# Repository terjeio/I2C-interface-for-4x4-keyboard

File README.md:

# I2C interface for 4x4 (or 5x5) keyboard with partial support for 2-key rollover and autorepeat.
Based on a Texas Instruments MSP430G2553 processor, uses a GPIO pin for signalling keypress events to host.
Example PCB is a KiCad project for the 20-pin DIP version MSP430G2553.

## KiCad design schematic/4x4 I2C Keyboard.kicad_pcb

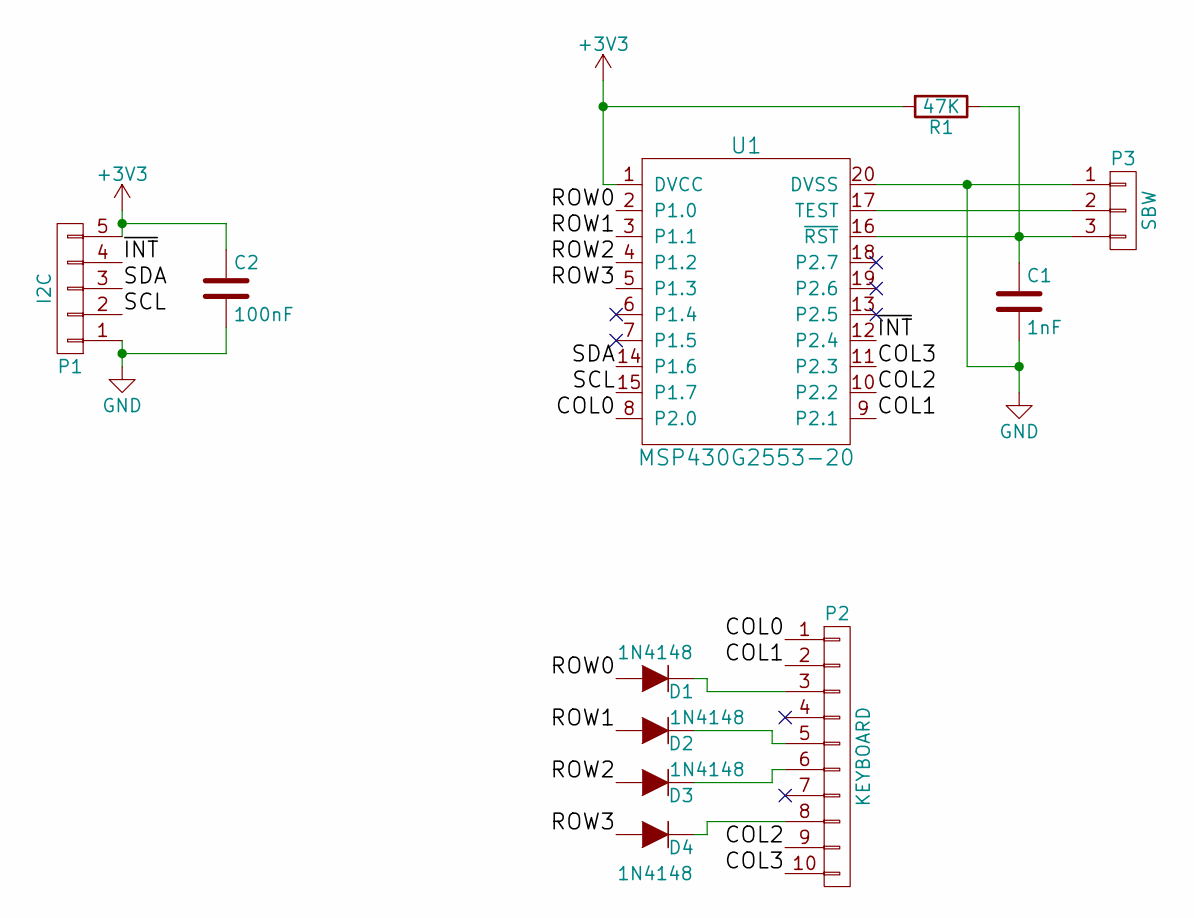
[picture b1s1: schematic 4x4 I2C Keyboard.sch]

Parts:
C1: 1nF; C_Disc_D5.0mm_W2.5mm_P2.50mm
C2: 100nF; C_Disc_D5.0mm_W2.5mm_P2.50mm
D1, D2, D3, D4: 1N4148; D_DO-41_SOD81_P7.62mm_Horizontal
P1: I2C; Pin_Header_Straight_1x05_Pitch2.54mm
P2: KEYBOARD; Pin_Header_Straight_1x10_Pitch2.54mm
P3: SBW; Pin_Header_Straight_1x03_Pitch2.54mm
R1: 47K; R_Axial_DIN0207_L6.3mm_D2.5mm_P10.16mm_Horizontal
U1: MSP430G2553-20; DIP-20_W7.62mm_Socket

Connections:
+3V3: C2.1, P1.5, R1.2, U1.1 (DVCC)
/COL0: P2.1, U1.8 (P2.0)
/COL1: P2.2, U1.9 (P2.1)
/COL2: P2.9, U1.10 (P2.2)
/COL3: P2.10, U1.11 (P2.3)
/ROW0: D1.2 (A), U1.2 (P1.0)
/ROW1: D2.2 (A), U1.3 (P1.1)
/ROW2: D3.2 (A), U1.4 (P1.2)
/ROW3: D4.2 (A), U1.5 (P1.3)
/SCL: P1.2, U1.15 (P1.7)
/SDA: P1.3, U1.14 (P1.6)
/~INT: P1.4, U1.12 (P2.4)
GND: C1.2, C2.2, P1.1, P3.1, U1.20 (DVSS)
unnamed: C1.1, P3.3, R1.1, U1.16 (~RST~)
unnamed: D1.1 (K), P2.3
unnamed: D2.1 (K), P2.5
unnamed: D3.1 (K), P2.6
unnamed: D4.1 (K), P2.8
unnamed: P3.2, U1.17 (TEST)

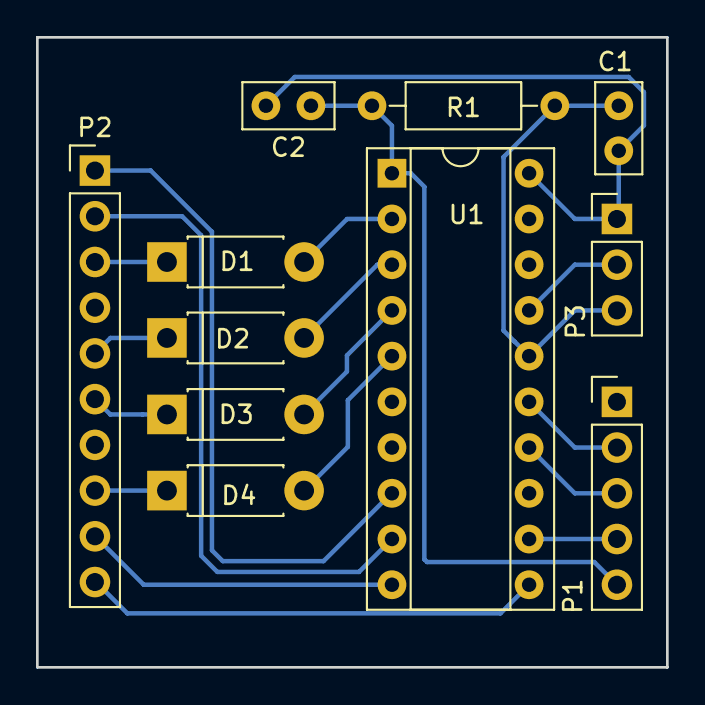
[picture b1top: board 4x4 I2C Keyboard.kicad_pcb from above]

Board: 2 copper layers, 35.0 x 35.0 mm, 11 parts (0 on the bottom side), 19 nets.

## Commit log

2017-05-16 :tada: Added .gitattributes
2017-05-16 added as new project
2017-05-16 changed description
2018-09-02 Simplified key mapping setup, added 5x5 matrix option

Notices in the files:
schematic/4x4 I2C Keyboard.kicad_pcb:
Licensed under CERN OHL v.1.2 or later
